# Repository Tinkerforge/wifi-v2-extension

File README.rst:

WIFI Extension 2.0
==================

This repository contains the hardware design files.
The software is included in the Master Brick software
and can be found at https://github.com/Tinkerforge/master-brick

Repository Content
------------------

hardware/:
 * Contains KiCad project files and additionally schematics as PDF

datasheets/:
 * Contains datasheets for sensors and complex ICs that are used

Hardware
--------

The hardware is designed with the open source EDA Suite KiCad
(http://www.kicad.org). Before you are able to open the files,
you have to install the Tinkerforge kicad-libraries
(https://github.com/Tinkerforge/kicad-libraries). You can either clone
them directly in hardware/ or clone them in a separate folder and
symlink them into hardware/
(ln -s kicad_path/kicad-libraries project_path/hardware). After that you
can open the .pro file in hardware/ with KiCad and from there view and
modify the schematics and the PCB layout.

Toolchain
---------

Clone and build toolchain from https://github.com/pfalcon/esp-open-sdk
into toolchain/ directory. The following instructions apply for ESP8266 SDK 1.5.3::

 sudo apt-get install build-essential gperf libtool libtool-bin help2man texinfo libncurses5-dev python2.7-dev autoconf
 mkdir toolchain
 cd toolchain
 git clone --recursive https://github.com/Tinkerforge/esp-open-sdk.git
 cd esp-open-sdk
 make STANDALONE=y VENDOR_SDK=1.5.3

Update toolchain::

 make clean
 git pull
 git submodule sync
 git submodule update
 make STANDALONE=y VENDOR_SDK=1.5.3

Additionally we use libesphttpd::

 cd toolchain
 git clone --recursive http://git.spritesserver.nl/libesphttpd.git/

To be able to build the extension firmware using libesphttpd a patch must be
applied to the ESP8266 SDK. This assumes that the toolchain is already
successfully built::

 cd software
 patch -b -N -d ../toolchain/esp-open-sdk/sdk/include -p1 < esp8266sdk-c_types.patch

libesphttpd must also be patched::

 cd software
 patch -b -N -d ../toolchain/libesphttpd -p1 < libesphttpd-Makefile.patch
 patch -b -N -d ../toolchain/libesphttpd -p1 < libesphttpd-httpd-nonos.patch

Build
-----

Provided that all the steps of the toolchain section was followed properly the
extension firmware can be built with::

 cd software
 make clean
 make

The compiled firmware can be found here::

 software/firmware/wifi_extension_v2_firmware.zbin

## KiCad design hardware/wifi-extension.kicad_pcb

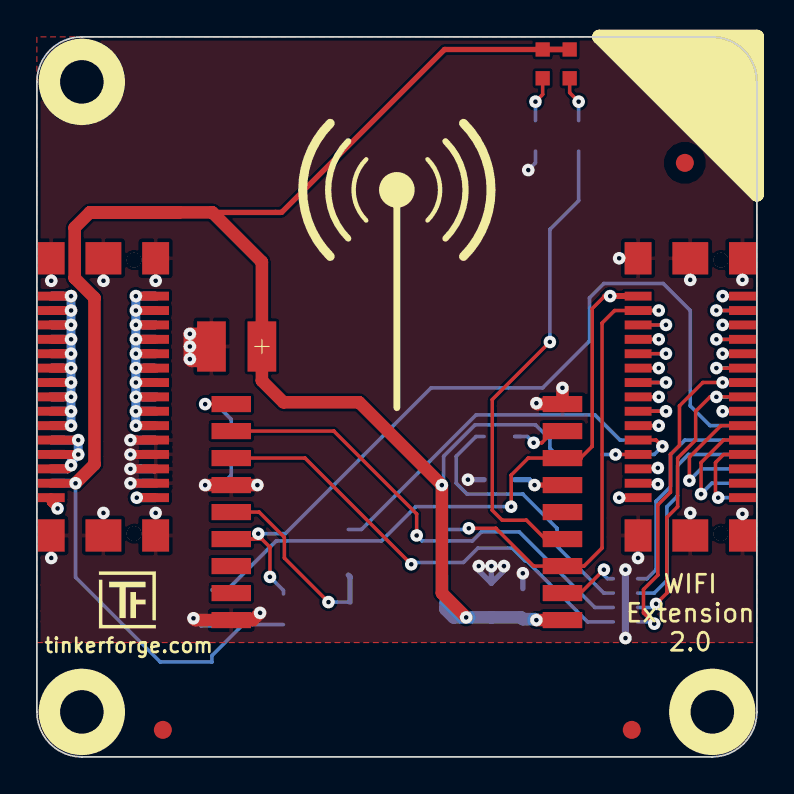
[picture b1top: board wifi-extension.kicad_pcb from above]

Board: 2 copper layers, 40.0 x 40.0 mm, 34 parts (0 on the bottom side), 49 nets.

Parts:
C1, C2: 100nF; C0603E
C3: 10µF; C0805E
C4: 100µF; 3528-21
D1: green; D0603
D2: blue; D0603
FILTER1: Filter-8x; DFN16-33x135
Fiducial_Mark: VAL**; Fiducial_Mark
Fiducial_Mark#2, Fiducial_Mark#3, Fiducial_Mark#4, Fiducial_Mark#5, Fiducial_Mark#6: VAL**; Fiducial_Mark
J1, J3: STACK-UP-HIGH; BTB08-ACS-TOP
J2, J4: STACK-DOWN; BTB08-ACS-BTM
P1, P2, P3: CONN_1; TSTPT
R1, R2, R4: 1k; R0603E
R3: 10k; R0603E
RP1, RP2: 1k; 0603X4
U1: M24C64; SOIC8
U2: ESP8266_WROOM02
U3, U4, U5, U6: DRILL; DRILL_NP
VAL: CE_5mm
VAL#2: WEEE_7mm_back

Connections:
3V3: C1.2, C2.2, C3.2, C4.1, D1.1, D2.1, J3.28, J4.28, P1.1, R3.1, R4.1, U1.8, U2.1
EEPROM_SEL: R2.1, U1.1, U2.14
EN: FILTER1.1, J2.21
GND: C1.1, C2.1, C3.1, C4.2, FILTER1.EXP, J1.EP, J2.EP, J3.21, J3.23, J3.25, J3.27, J3.EP, J4.21, J4.23, J4.25, J4.27, J4.EP, P3.1, R1.2, R2.2, RP1.1, RP2.8, U1.2, U1.4, U2.9, U2.13, U2.18
IO0: FILTER1.3, J2.23
LED: RP2.5, U2.4
unnamed: D1.2, RP2.4
unnamed: D2.2, RP2.1
unnamed: FILTER1.10, U2.12
unnamed: FILTER1.12, U2.11
unnamed: FILTER1.14, RP1.4
unnamed: FILTER1.16, U2.2
unnamed: J1.1, J2.1
unnamed: J1.3, J2.3
unnamed: J1.5, J2.5
unnamed: J1.6, J2.6
unnamed: J1.7, J2.7
unnamed: J1.8, J2.8
unnamed: J1.9, J2.9
unnamed: J1.10, J2.10
unnamed: J1.11, J2.11
unnamed: J1.12, J2.12
unnamed: J1.14, J2.14
unnamed: J1.16, J2.16
unnamed: J1.17, J2.17
unnamed: J1.18, J2.18
unnamed: J1.19, J2.25
unnamed: J1.20, J2.20
unnamed: J1.21, J2.27
unnamed: J1.22, J2.24
unnamed: J1.23, J2.29
unnamed: J1.24, R4.2
unnamed: J1.26, J2.26
unnamed: J1.28, J2.28
unnamed: J1.30, J2.30
unnamed: J3.1, J3.3, J3.5, J3.7, J3.9, J3.11, J3.13, J3.15, J3.17, J3.19, J4.1, J4.3, J4.5, J4.7, J4.9, J4.11, J4.13, J4.15, J4.17, J4.19
unnamed: J3.2, J3.4, J3.6, J3.8, J3.10, J3.12, J3.14, J3.16, J3.18, J3.20, J4.2, J4.4, J4.6, J4.8, J4.10, J4.12, J4.14, J4.16, J4.18, J4.20
unnamed: J3.22, J3.24, J3.26, J4.22, J4.24, J4.26
unnamed: J3.29, J4.29
unnamed: J3.30, J4.30
unnamed: R1.1, U2.10
unnamed: RP1.5, U2.8
unnamed: RP1.8, U2.6
RX: FILTER1.7, J1.13, J2.13
SCL: J1.4, J2.4, U1.6, U2.3
SDA: J1.2, J2.2, P2.1, U1.5, U2.7
SELECT: J2.22, U1.3
TX: FILTER1.5, J1.15, J2.15
nRESET: J2.19, R3.2, U2.15

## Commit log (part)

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2015-07-27 initial commit for wifi v2 extension
2015-07-27 fix header
2015-07-27 Add datasheets
2015-07-27 prototype finished
2015-08-07 change schematic description of 2. page
2015-08-13 change rx/tx interface to extension SPI interface
2015-09-07 Add initial (pre-cleanup) version of WIFI 2.0 code
    This is a "rapid-prototype" that still needs major cleanup
    and restructuring. The UART protocol implementation seems
    to be working and stable, so we can always compare a cleaned up
    version to this commit.
2015-09-07 Fix RST
2015-09-09 add license file
2015-09-22 Add I2C, EEPROM, brickd, authentication
2015-09-25 Add support for http and websocket
2015-09-25 Update documentation
2015-09-25 fully routed
2015-09-28 Add status getter implementation
2015-10-14 updated schematic
2015-10-14 ordered prototype
2015-10-26 remove antenna symbol, move ce and weee logo
2015-12-29 Add ld script and update Makefile
2016-02-09 Add WIP marker
2016-02-24 ordered version
2016-05-27 Add test folder
2016-06-10 add get_wifi2_firmware_version api
2016-06-17 Integrate libesphttpd build with firmware build.
2016-06-17 Add .gitignore
2016-06-18 Update Makefile
2016-06-18 Renaming path file
2016-06-18 Fix typo in patch file name
2016-06-24 Adding web interface
2016-06-24 Fix status table layout in smaller size and a little directory restructure
2016-06-24 Add some form dynamics
2016-06-26 Skeleton implementation for proceeding with session cookie implementation
2016-06-27 Add hint to install gperf package
2016-06-27 Rename save_wifi2_configuration return variable to match common naming pattern
2016-06-30 Add changelog commit after the fact
2016-07-02 Bring the whole web interface into one single God HTML file
2016-07-05 Initial implementation of session cookie based authentication if secret is enabled
2016-07-08 Only show body of the page after the page is ready.
2016-07-08 Initial get status implementation
2016-07-09 Implementation of RX/TX packet count
2016-07-09 Integrate RX/TX packet count on Web interface
2016-07-10 Set proper initial signal strength progress bar colour
2016-07-10 Patch for counting httpd packets
2016-07-11 Authenticate page secret show/hide checkbox implementation
2016-07-11 Consistent naming
2016-07-15 Fix session ID leak resulting from cached authnentication page
2016-07-15 add missing schematic
2016-07-15 Consistent authentication behaviour for browser sessions having the same session ID
2016-07-21 Add more dependencies
2016-07-22 Fix copy and paste error in configuration application procedure
2016-07-29 Little cleanup
2016-07-29 Fix Base64 image and logic for populating some fields of configuration editor
2016-07-29 Initial implementation of settings viewing
2016-08-03 User feedback based on dialogs. Fix off by one error for AP netmask and gateway.
2016-08-05 Add ping pong CGI function and add validation GUI elements
2016-08-12 Consistent request ID checks
2016-08-15 Return key to login
2016-08-15 For disabling logo anchor
2016-08-15 Content of about dialog and timeout constants
2016-09-09 Client side submission fixes
2016-09-10 Partial POST data arrival handler and submission of general settings. Proper redirection after save and reset.
2016-09-10 Highlight submit buttons
2016-09-13 Implementation of AP settings submit and proper length limits.
2016-09-19 Enable/disable the web interface using web site port
2016-09-21 Fix client mode AP BSSID check
2016-09-21 Add note about AP mode channel configuration
2016-09-23 Limit input to maximum 63 characters of authentication page's secret input
2016-09-23 Fix authenticate button logic
2016-09-25 Initial integration of SHA-1 HMAC based secret handling
2016-09-28 Remove .temp files while building the front end of the web interface
2016-09-29 Fix port input dynamic validation handling
2016-09-29 Fix beforeunload logic
2016-10-01 Backward compatibility for brickv 2.3.6
2016-10-01 Consistent validation with brickv
2016-10-07 Fix typos
2016-10-08 Fix typo
2016-10-13 Fix handling of potentially non-NUL-terminated strings
2016-10-13 web: Use correct maxlength for authentication secret
2016-10-13 Update version number and changelog
2016-10-13 Update changelog again
2016-10-17 Fix typo and data type
2016-10-21 Add missing ESP8266 SDK firmware configration binaries
    Without those the firmware would not boot correctly.
2016-10-24 Update linker script
    Add *libmbedtls.a:(.literal .text .literal.* .text.*)
2016-10-24 add autoconf to apt-get
2016-10-25 Update changelog
2016-11-02 Add ringbuffer for outgoing data
2016-11-02 Add remove function to ringbuffer
2016-11-02 Add hold/unhold support
2016-11-02 Remove double declaration
2016-11-02 Add 2.0.3 changelog entry
2016-11-03 Fix to be able to access EEPROM when debug is on
2016-11-04 Update required package list in readme
2016-11-04 Add mesh networking realted documents
2016-11-04 Get rid of flash mode switching hack
2016-11-08 Update mesh library
2016-11-09 Enable output while updating the mesh library
2016-11-11 Add mesh server for testing and experiments
2016-11-11 Consistent debug output
2016-11-11 Track and print total connected clients
2016-11-11 Mesh traffic handling
2016-11-14 Send test packet after a certain time interval but only after receiving a response of the packet sent by the node.
2016-11-14 Send test packet without check on each receive
2016-11-14 Don't explicitly set WiFi station config for mesh mode
2016-11-15 New config struct for mesh
2016-11-15 Update static mesh router BSSID
2016-11-16 Cleanup mesh configuration
2016-11-16 Update document
2016-11-18 Cleanup configuration apply logic, read configuration from new configuration struct print mesh related status info on system init done callback
2016-11-18 Try to enable disable Nagel's algorithm
2016-11-18 Revert to previous non EEPROM config read when debug enabled mechanism
2016-11-18 Bring back fix to access EEPROM regardless of whether debug is turned on or off. The WiFi station connection problem seems to be introduced by the 6 libraries that are used from ESP mesh git reposito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
2016-11-18 Comment out updating libraries from the ESP mesh repository since updating these libraries introduces the problem where even simple station mode connection fails
2016-11-18 Update comment
2016-11-19 Firmware uses non-OS SDK version 1.5.3 which works properly with the latest mesh library
2016-11-19 Update c_types.h patch for SDK 1.5.3 switch
2016-11-19 Rename document
2016-11-20 Remove unused files
2016-11-20 Reduce amount of debug output
2016-11-21 Implement setter and getter for mesh configuration. Integrate the existing mesh code to proper configuration management
2016-11-23 Reduce mesh debug output
2016-11-24 Initial mesh integration
2016-11-24 Integrate mesh status
2016-11-25 Set/get mesh mdoe station hostname properly
2016-11-25 Modify debug output
2016-11-25 Handle wrong configuration state that can be caused by older brickv when being used with newer extension firmware which already had mesh mode enabled
2016-11-25 Remove FIXME tag
2016-11-28 Forward and handle TFP packets from mesh layer to existing TFP handling layer
2016-11-30 Use website config parameter to enable/disable web interface
2016-11-30 Rename config parameters, server_ip and server_port to gateway_ip and gateway_port and new currently unused parameter gateway hostname
2016-11-30 Update libmesh
2016-12-12 Send buffer support which enables sending packet from previous packet's sent callback. This is the suggested way to send packets using ESP8266 SDK
2016-12-13 Call function on TFP layer
2016-12-17 Implementation of initial mesh transport
2016-12-21 Implementation of mesh transport
2016-12-21 Register disconnect callback with the connect callback
2016-12-22 Improve received packet handling
2016-12-22 Get rid of stack enumerate function and types
2016-12-29 Implementation under test
2017-01-03 Buffer size fix and root node ping reply feature
2017-01-03 Fix hostname formation problem when mesh prefix is of maximum length
2017-01-03 Mesh mode router SSID maximum length fix for API calls
2017-01-04 It is better to keep the struct sizes consistent with the API argument data sizes
2017-01-04 Hold/unhold implementation for mesh
2017-01-04 Define wasn't unused, sorry!
2017-01-04 Elaborate send fail log message
2017-01-04 Reduce mesh send buffer size to conserve memory
2017-01-05 Configure do ping timer as a free running timer
2017-01-10 Handle mesh router SSID of 32 characters
2017-01-19 Remove tabs
2017-01-19 Return error if brickd function is not implemented
2017-01-19 add tfp message error codes
2017-01-19 Remove unnecessary tabs and indentation
2017-01-19 Change method name
2017-01-19 Adapt to API naming changes
2017-01-23 Make extension reset reliable
2017-01-23 Add 2.1.0 changelog
2017-01-23 Add changelog commit refs
2017-01-30 Do setter/getter operation on the configuration that is kept in EEPROM
2017-02-20 Fix indentation
2017-02-24 Increase routing table size from 10 to 16
2017-02-24 Add TODO
2017-02-24 Increase versionto 2.1.2
2017-02-24 Don't try to send data if our receive buffer is full, we very likely just didn't yet parse the ACK yet in this case
2017-02-24 Sanity-check length properly
2017-02-24 We clear the receive buffer after a message if it was full at the start of the state machine (the next message is likely broken)
2017-02-24 Use finish callback for websockets
2017-02-24 Remove unnecessary comment
2017-02-24 Add send check and write finish prototypes
2017-02-24 Add buffer length and min heap size variables
2017-02-24 Initialize buffer length to 0
2017-02-24 Call brickd_disconnect at beginning of connect callback, to remove all routes that are still there and now definitely not correct anymore
2017-02-24 Remove out-commented code
2017-02-24 Use finish callback instead of sent callback
2017-02-24 Use finish callback
2017-02-24 We can only send new data if send buffer is also empty
2017-02-24 Check return value of send properly
2017-02-24 Move route match removal to correct position (after we tested if we can send data)
2017-02-24 Add first changes for 2.1.2 to changelog
2017-02-28 Add route removal function to reduce duplicated code
2017-02-28 Remove TODO (we don't have to check again here)
2017-02-28 Set NULL correctly to pointer
2017-02-28 Add more debug output to brickd routing debug function
2017-02-28 Add length-check for received data
2017-02-28 Remove unnecessary current_match temporary variable
2017-02-28 Remove code duplication
2017-05-05 Remove support for wifi password getter
2017-05-11 Add changelog and increase version for release
2017-05-11 Add date and ref of commit
2017-09-15 Add 3d information (final)
2018-02-20 Cleanup KiCad libraries config
    Ensure LibDir=kicad-libraries and LibName1=tinkerforge.
    Remove special library.
2018-11-26 Fix libesphttpd patches for current version of libesphttpd
2019-07-23 Add hint about debug configuration
2020-01-17 Try 3 times to load config from EEPROM before giving up
    Also don't overwrite unloadable config to give it a chance on the
    next boot.
2020-01-17 Whitespace
2020-01-17 Make get-wifi2-mesh-router-password always report an empty string
2020-01-17 Add missing defines for strnlen function
2020-01-17 Make client and mesh router password getters return fake passwords
    This allows brickv to distinguish between "no encryption" and WPA2
    mode. In contrast to the AP encryption mode, there is no extra config
    value that represents the client and mesh router encryption mode.
2020-01-20 Fine tune changelog
2021-10-25 Update KiCad link
    https://www.kicad.org/blog/2021/10/Avoid-links-to-former-kicad-domain/
2021-12-15 Use local copy of esp-open-sdk.git
2021-12-15 Add commit ref to changelog
2021-12-17 Avoid crash when using mesh functions in non-mesh mode
    Closes #2.

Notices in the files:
hardware/wifi-extension.kicad_pcb:
Licensed under CERN OHL v.1.1
Copyright (©) 2015, B.Nordmeyer
Copyright Tinkerforge GmbH 2015.
This documentation describes Open Hardware and is licensed under the
CERN OHL v. 1.1.
